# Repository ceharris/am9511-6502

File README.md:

AM9511 Interface Module for the 6502
====================================

The AMD AM9511 Arithmetic Processing Unit, first produced in the late 
1970s, provides hardware support for high performance fixed and floating 
point arithmetic and a variety of floating point trigonometric and 
mathematical operations, for use with microprocessors of that period.

This repository provides schematics and board design for a module that
can be connected to the 6502 bus interface, allowing the AM9511 to be 
addressed as an I/O device. The design is adapted from the work of 
Kissel and Currie[1] in which they developed an experiment using a 6502 
microprocessor to control four AM9511A floating-point arithmetic units, 
and from Hart’s MICROCRUNCH[2] which also used the AM9511A (Intel 8231A) 
interfaced with a (Rockwell) 6502.

The specification here anticipates the use of an AM9511A clocked at
4 MHz. However, the same design will work with earlier versions of the 
AM9511, by swapping the 4 MHz clock oscillator with a unit of an 
appropriately lower speed.

See [am9511-6502-description.pdf](am9511-6502-description.pdf) for a
full description of the interface circuit design and 
[am9511-6502-schematic.pdf](am9511-6502-schematic.pdf) for the schematic.

This repository contains the full KiCad sources for the schematic and a 
PCB design for the module. 

The `logic` folder contains the programming details for the ATF16V8B
used in the circuit, as produced by [Galette](https://github.com/simon-frankau/galette) from the `am9511-6502.pld` source file. The provided JEDEC file
(`am9511-6502.jed`) can be easily programmed into an ATF16V8B using 
[minipro](https://gitlab.com/DavidGriffith/minipro).

Also included in the `docs` folder are source documents cited below, as 
well as datasheets and supplementary documents for the AM9511.

---
1. Kissel, R and Currie, J: "Hardware Math for the 6502 Microprocessor"; 
   July 1985; NASA TM-86517
2. Hart, J: "MICROCRUNCH: An Ultra-Fast Arithmetic Computing System 
   (part 1)"; August 1981; MICRO - the 6502/6809 Journal (No. 39)

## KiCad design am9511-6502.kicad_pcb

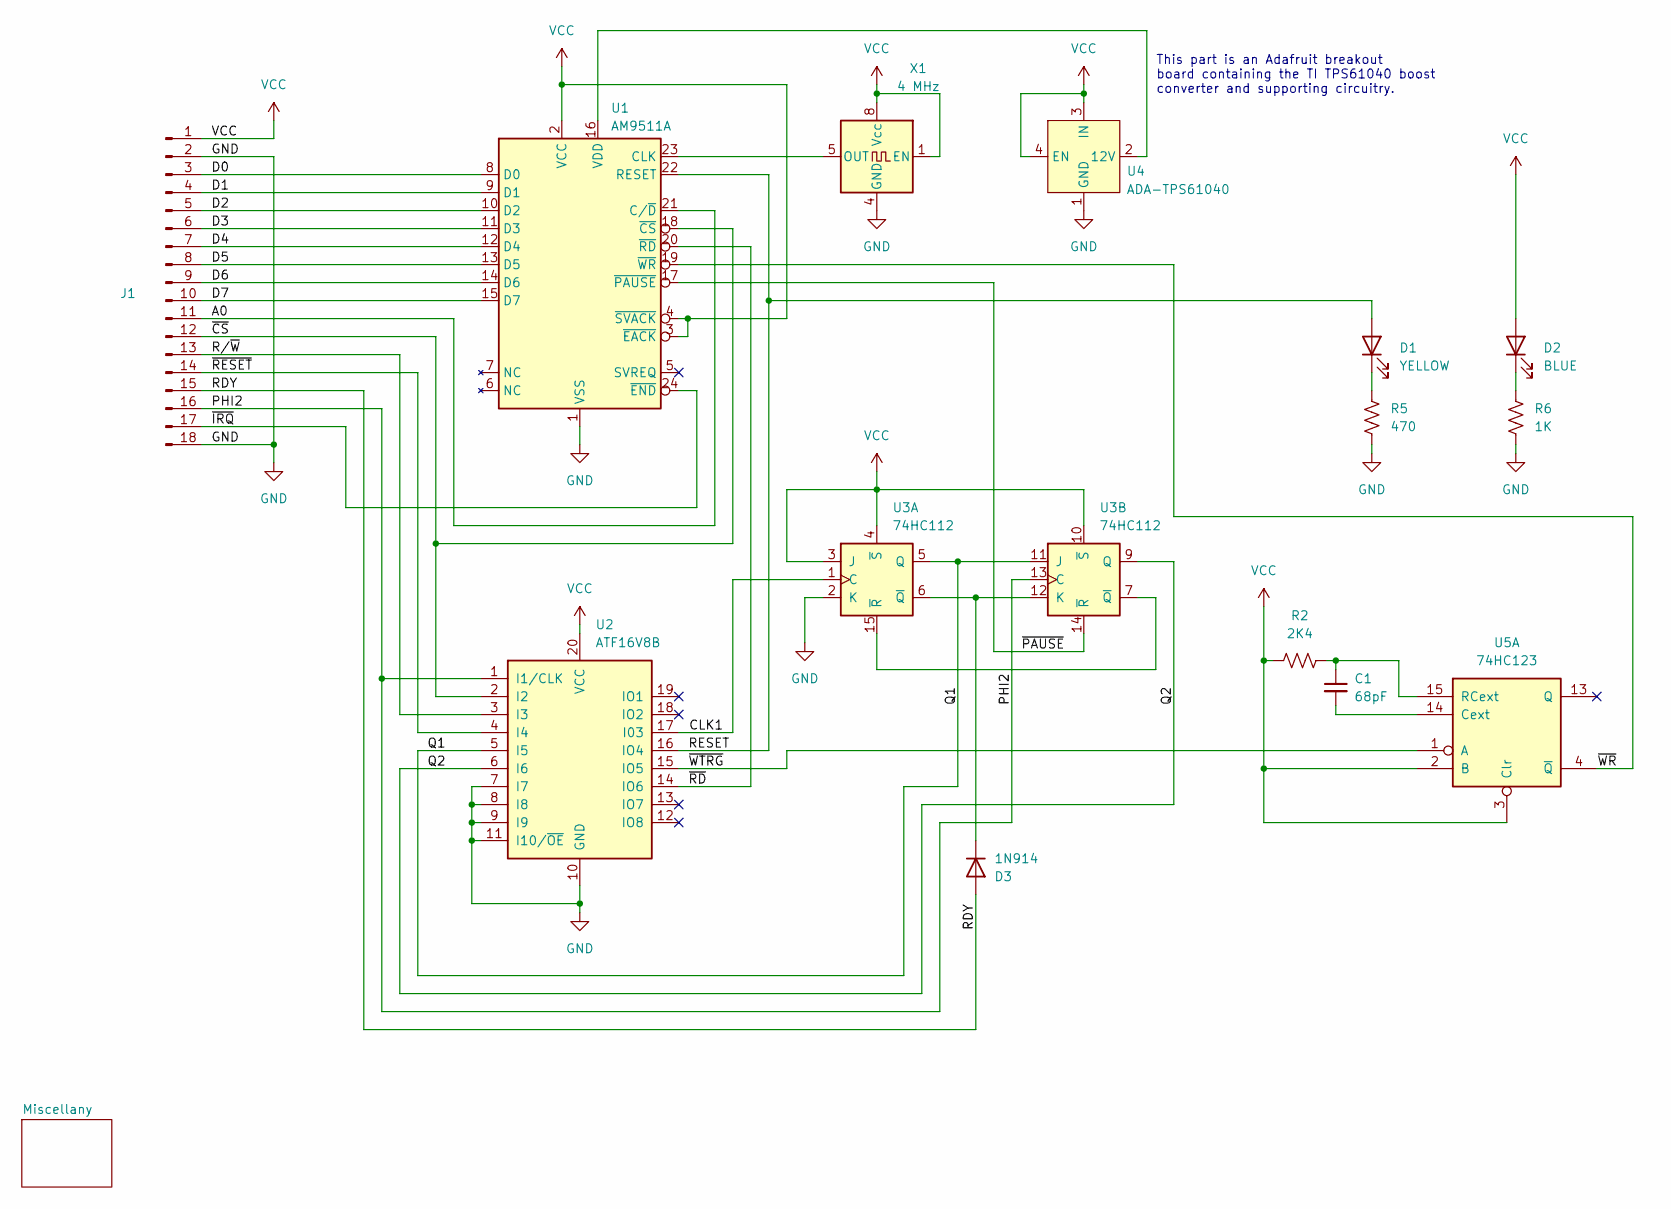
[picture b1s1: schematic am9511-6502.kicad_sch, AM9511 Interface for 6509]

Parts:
C1: 68pF; C_Disc_D5.0mm_W2.5mm_P5.00mm
D1: YELLOW; LED_D5.0mm
D2: BLUE; LED_D5.0mm
D3: 1N914; D_DO-35_SOD27_P7.62mm_Horizontal
J1: Conn_01x18_Pin; PinHeader_1x18_P2.54mm_Horizontal
R2: 2K4; R_Axial_DIN0207_L6.3mm_D2.5mm_P7.62mm_Horizontal
R5: 470; R_Axial_DIN0207_L6.3mm_D2.5mm_P7.62mm_Horizontal
R6: 1K; R_Axial_DIN0207_L6.3mm_D2.5mm_P7.62mm_Horizontal
U1: AM9511A; DIP-24_W15.24mm_Socket
U2: ATF16V8B; DIP-20_W7.62mm_Socket
U3: 74HC112; DIP-16_W7.62mm_Socket
U4: ADA-TPS61040
U5: 74HC123; DIP-16_W7.62mm_Socket
X1: 4 MHz; Oscillator_DIP-8

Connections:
/A0: J1.11, U1.21 (C/~D)
/CLK1: U2.17 (I03), U3.1 (C)
/D0: J1.3, U1.8 (D0)
/D1: J1.4, U1.9 (D1)
/D2: J1.5, U1.10 (D2)
/D3: J1.6, U1.11 (D3)
/D4: J1.7, U1.12 (D4)
/D5: J1.8, U1.13 (D5)
/D6: J1.9, U1.14 (D6)
/D7: J1.10, U1.15 (D7)
/PHI2: J1.16, U2.1 (I1/CLK), U3.13 (C)
/Q1: U2.5 (I5), U3.5 (Q), U3.11 (J)
/Q2: U2.6 (I6), U3.9 (Q)
/RDY: D3.2 (A), J1.15
/RESET: D1.2 (A), U1.22 (RESET), U2.16 (IO4)
/R/~W: J1.13, U2.3 (I3)
/~CS: J1.12, U1.18 (~CS), U2.2 (I2)
/~IRQ: J1.17, U1.24 (~END)
/~PAUSE: U1.17 (~PAUSE), U3.14 (~R)
/~RD: U1.20 (~RD), U2.14 (IO6)
/~RESET: J1.14, U2.4 (I4)
/~WR: U1.19 (~WR), U5.4 (~Q)
/~WTRG: U2.15 (IO5), U5.1 (A)
GND: J1.2, J1.18, R5.2, R6.2, U1.1 (VSS), U2.7 (I7), U2.8 (I8), U2.9 (I9), U2.10 (GND), U2.11 (I10/~OE), U3.2 (K), U4.1 (GND), X1.4 (GND); also elsewhere on the board
unnamed: D1.1 (K), R5.1
unnamed: D2.1 (K), R6.1
unnamed: D3.1 (K), U3.6 (~Q), U3.12 (K)
unnamed: U1.23 (CLK), X1.5 (OUT)
unnamed: U1.16 (VDD), U4.2 (12V)
unnamed: U3.7 (~Q), U3.15 (~R)
unnamed: C1.2, U5.14 (Cext)
unnamed: C1.1, R2.2, U5.15 (RCext)
VCC: D2.2 (A), J1.1, R2.1, U1.2 (VCC), U1.3 (~EACK), U1.4 (~SVACK), U2.20 (VCC), U3.3 (J), U3.4 (~S), U3.10 (~S), U4.3 (IN), U4.4 (EN), U5.2 (B), U5.3 (Clr), X1.1 (EN), X1.8 (Vcc); also elsewhere on the board

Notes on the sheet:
This part is an Adafruit breakout board containing the TI TPS61040 boost converter and supporting circuitry.

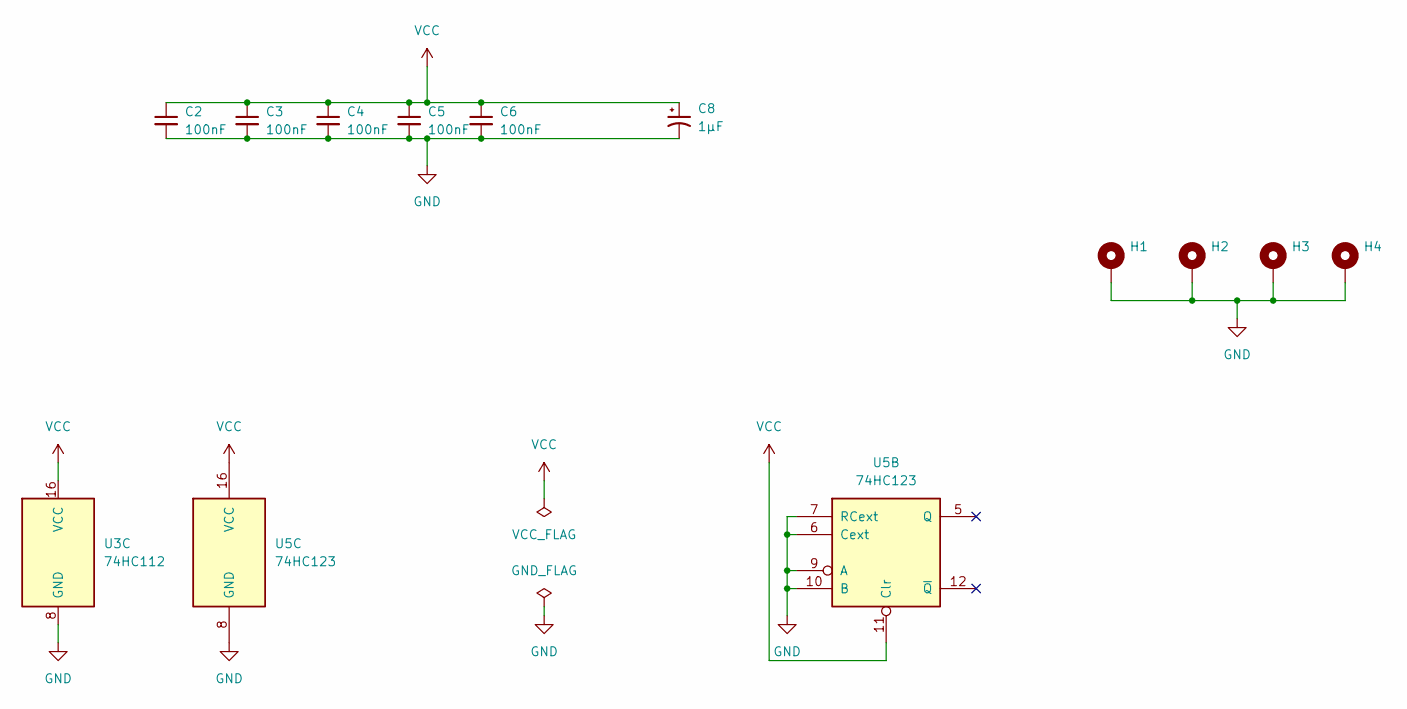
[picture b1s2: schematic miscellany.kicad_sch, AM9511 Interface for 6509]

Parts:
C2, C3, C4, C5, C6: 100nF; C_Disc_D5.0mm_W2.5mm_P2.50mm
C8: 1µF; CP_Radial_D5.0mm_P2.50mm
H1, H2, H3, H4: MountingHole_Pad; MountingHole_2.2mm_M2_DIN965_Pad
U3: 74HC112; DIP-16_W7.62mm_Socket
U5: 74HC123; DIP-16_W7.62mm_Socket

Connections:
GND: C2.2, C3.2, C4.2, C5.2, C6.2, C8.2, H1.1, H2.1, H3.1, H4.1, U3.8 (GND), U5.6 (Cext), U5.7 (RCext), U5.8 (GND), U5.9 (A), U5.10 (B); also elsewhere on the board
VCC: C2.1, C3.1, C4.1, C5.1, C6.1, C8.1, U3.16 (VCC), U5.11 (Clr), U5.16 (VCC); also elsewhere on the board

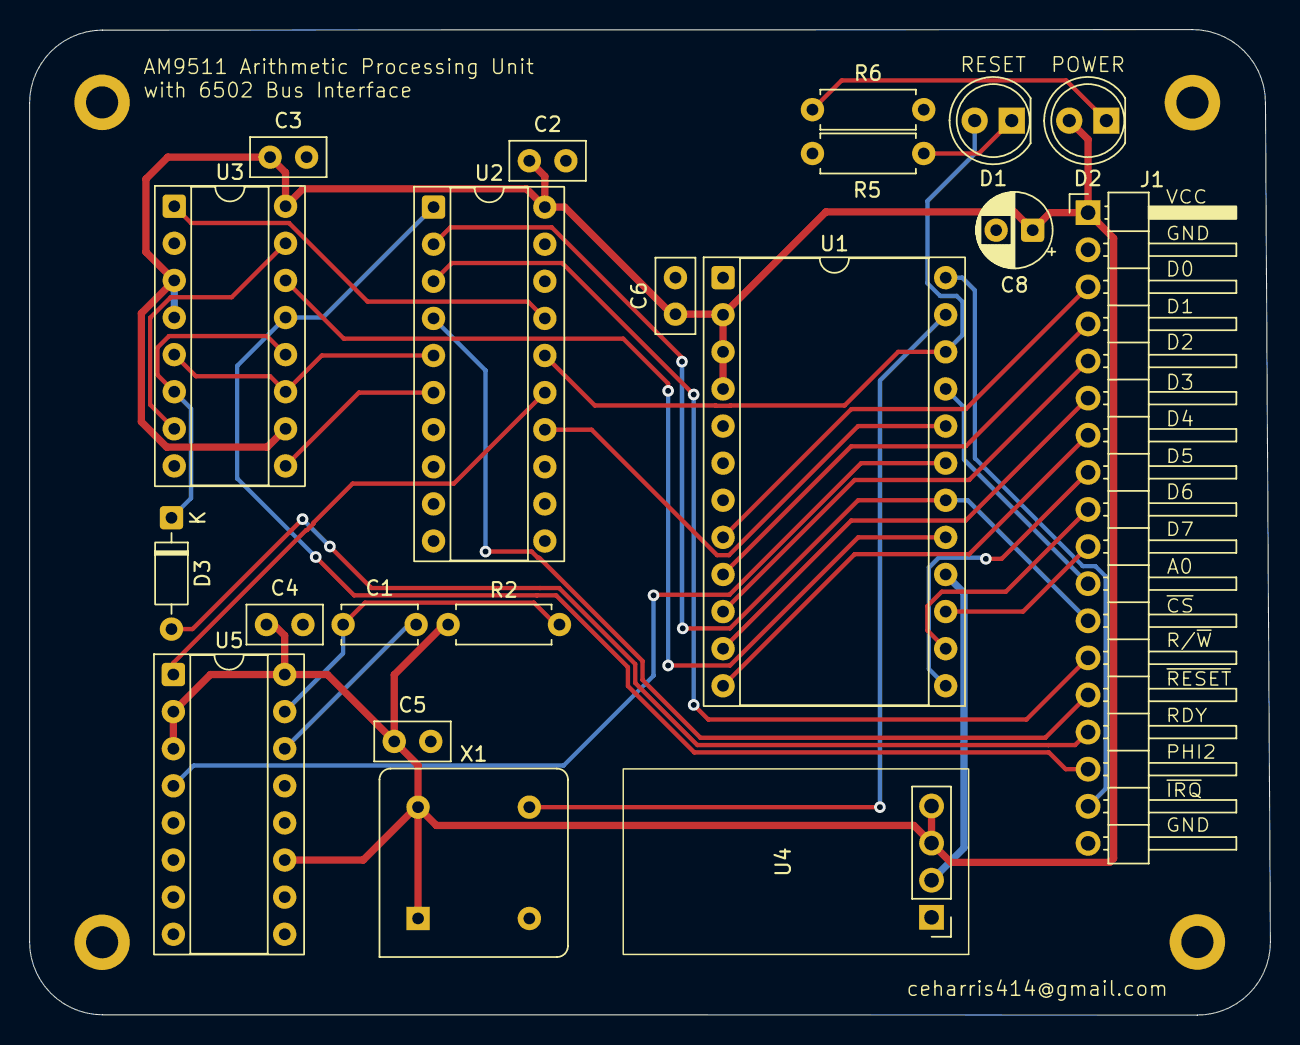
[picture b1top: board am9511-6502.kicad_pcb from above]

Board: 2 copper layers, 84.9 x 67.5 mm, 24 parts (0 on the bottom side), 33 nets.

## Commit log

2025-06-04 move custom symbols and footprints to project libraries
2025-06-04 added documentation
2025-06-04 format README footnotes
2025-06-04 additional README detail
2025-06-04 add small schematic image
2025-06-04 README tweaks
2025-06-04 minor corrections in am9511-logic.pld description
2025-06-04 rename doc to fix surname mispelling
2025-06-04 remove IEEE article from repo
